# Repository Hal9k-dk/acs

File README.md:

# Hal9k Access Control System

For more information, see https://hal9k.dk/access-control-system/.

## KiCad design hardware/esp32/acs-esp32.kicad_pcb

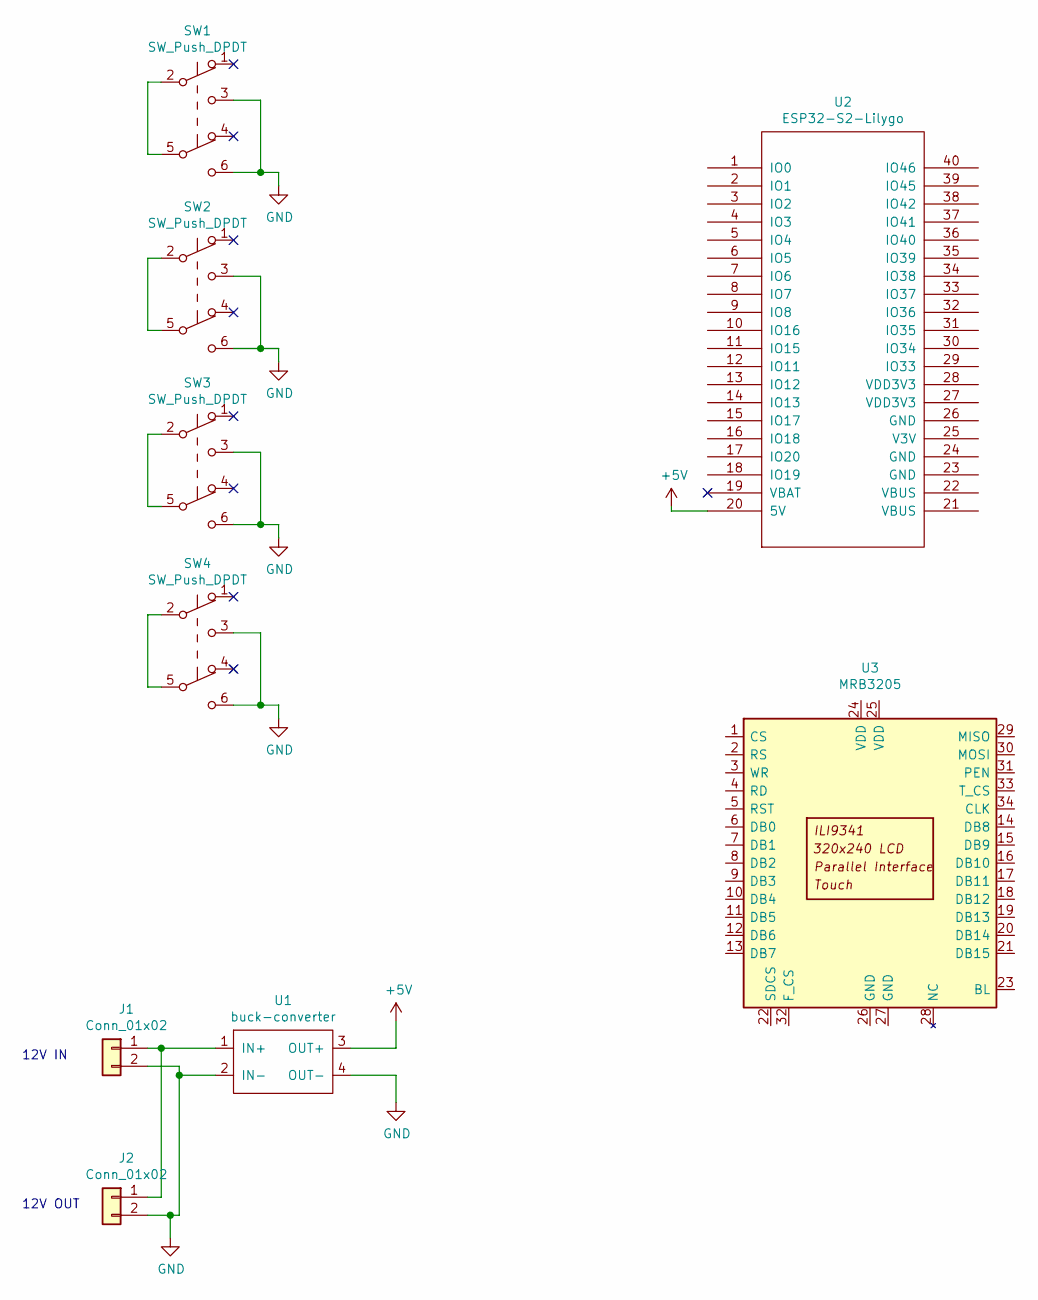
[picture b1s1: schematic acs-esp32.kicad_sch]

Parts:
J1, J2: Conn_01x02; JST_XH_B02B-XH-A_1x02_P2.50mm_Vertical
SW1, SW2, SW3, SW4: SW_Push_DPDT; SW_PUSH_8.5x8.5_DPDT
U1: buck-converter
U2: ESP32-S2-Lilygo; DIP-40_W25.4mm
U3: MRB3205; PinHeader_2x17_P2.54mm_Vertical

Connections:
+5V: U1.3 (OUT+), U2.20 (5V)
GND: J1.2, J2.2, SW1.3 (C), SW1.6 (C), SW2.3 (C), SW2.6 (C), SW3.3 (C), SW3.6 (C), SW4.3 (C), SW4.6 (C), U1.2 (IN-), U1.4 (OUT-)
unnamed: J1.1, J2.1, U1.1 (IN+)
unnamed: SW1.2 (B), SW1.5 (B)
unnamed: SW2.2 (B), SW2.5 (B)
unnamed: SW3.2 (B), SW3.5 (B)
unnamed: SW4.2 (B), SW4.5 (B)

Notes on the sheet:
12V IN
12V OUT

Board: 2 copper layers, 9 parts (0 on the bottom side), 7 nets, no tracks yet.

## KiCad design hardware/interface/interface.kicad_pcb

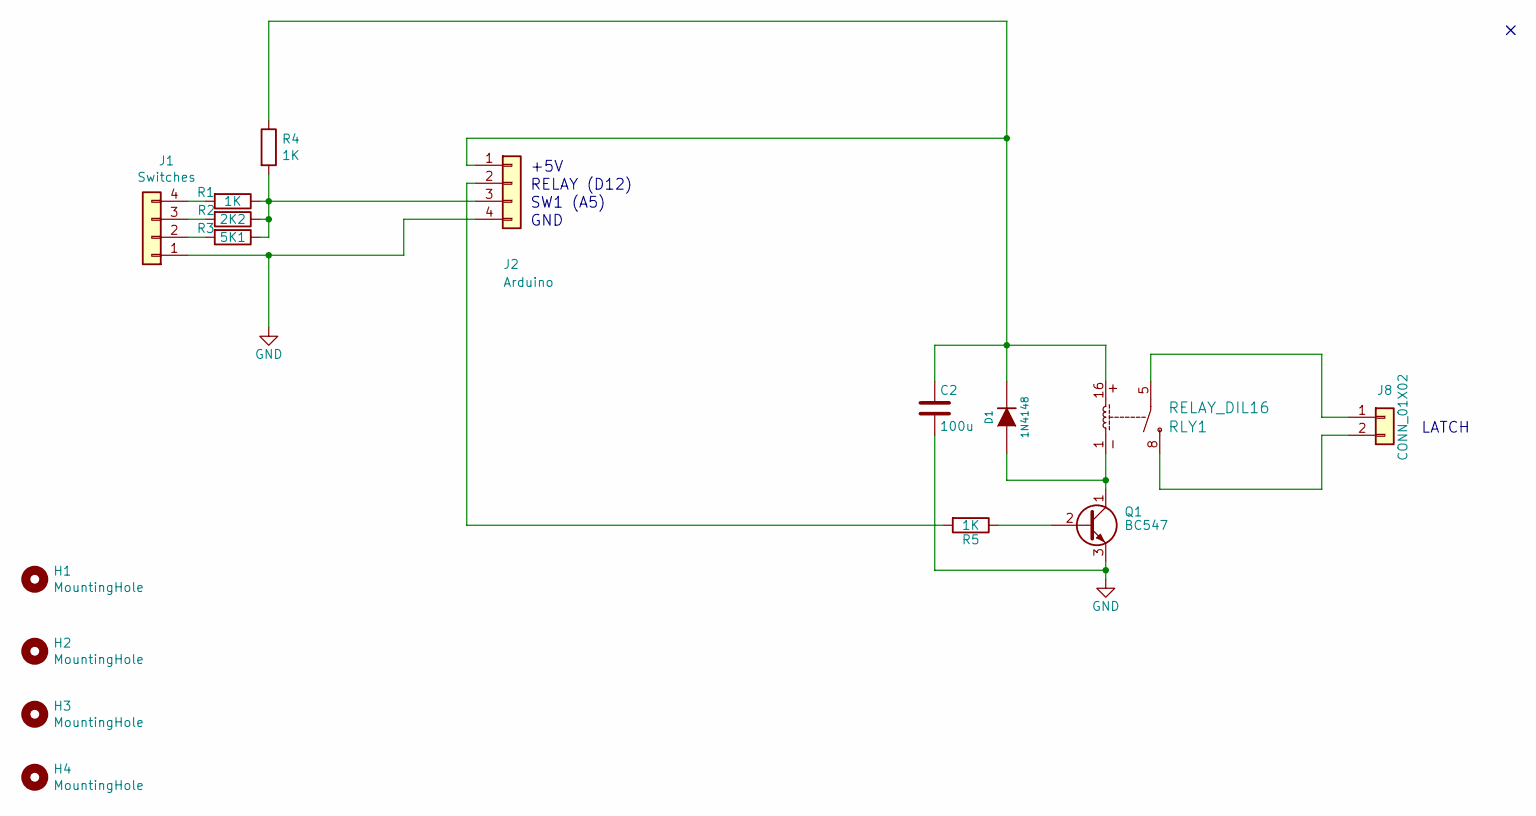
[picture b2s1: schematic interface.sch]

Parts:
C2: 100u; CP_Radial_D10.0mm_P5.00mm
D1: 1N4148; D_DO-35_SOD27_P2.54mm_Vertical_AnodeUp
H1, H2, H3, H4: MountingHole; MountingHole_2.7mm_M2.5
J1: Switches; JST_XH_B04B-XH-A_1x04_P2.50mm_Vertical
J2: Arduino; PinHeader_1x04_P2.54mm_Vertical
J8: CONN_01X02; JST_XH_B02B-XH-A_1x02_P2.50mm_Vertical
Q1: BC547; TO-92_Wide
R1, R4, R5: 1K; R_Axial_DIN0309_L9.0mm_D3.2mm_P5.08mm_Vertical
R2: 2K2; R_Axial_DIN0309_L9.0mm_D3.2mm_P5.08mm_Vertical
R3: 5K1; R_Axial_DIN0309_L9.0mm_D3.2mm_P5.08mm_Vertical
RLY1: RELAY_DIL16; DIP-16_Relay

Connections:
GND: C2.2, J1.1, J2.4, Q1.3 (E)
unnamed: C2.1, D1.2 (K), J2.1, R4.1, RLY1.16
unnamed: D1.1 (A), Q1.1 (C), RLY1.1
unnamed: J1.2, R3.2
unnamed: J1.3, R2.2
unnamed: J1.4, R1.2
unnamed: J2.2, R5.2
unnamed: J2.3, R1.1, R2.1, R3.1, R4.2
unnamed: J8.1, RLY1.5
unnamed: J8.2, RLY1.8
unnamed: Q1.2 (B), R5.1

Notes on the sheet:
LATCH
GND
+5V
RELAY (D12)
SW1 (A5)

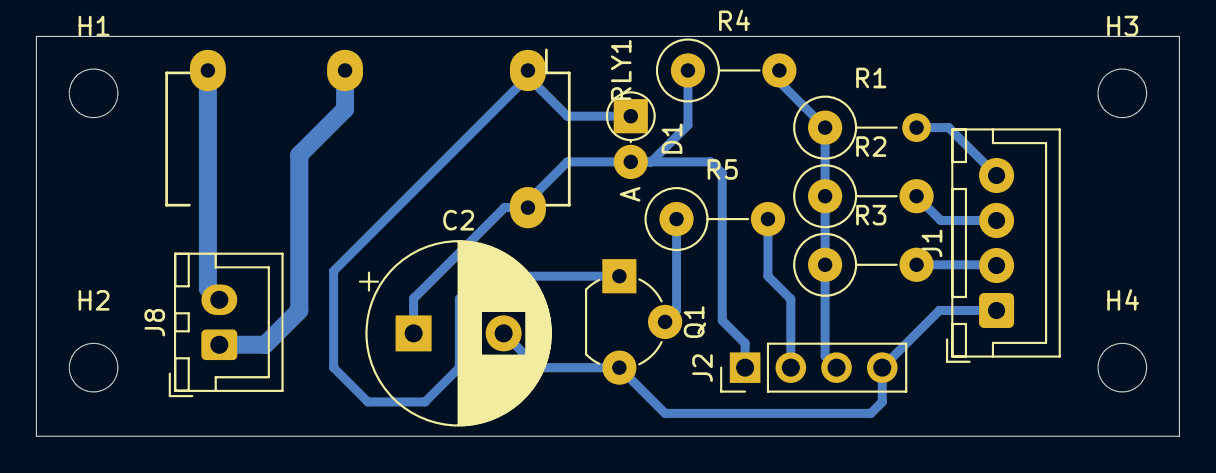
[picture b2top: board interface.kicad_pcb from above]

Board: 2 copper layers, 63.5 x 22.2 mm, 16 parts (0 on the bottom side), 11 nets.

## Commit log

2018-10-27 Add link.
2018-10-27 Include user name.
2018-10-28 Add missing file.
2019-03-14 Check user.active.
2019-03-31 Update.
2019-05-17 Port to OpenSmart HX8352-B display.
2019-05-17 Add test.
2019-05-17 Fix bugs.
2019-05-17 Clear clock.
2019-05-18 Add PCB for switches and relay.
2019-05-18 Enable pullups on switch pins.
2019-05-26 Fix clear for 'c'. Prepare for analog switch input.
2019-05-26 Stuff.
2019-05-26 Read analog switch input.
2019-06-22 Update versions.
2019-06-22 Get rid of warnings.
2019-06-24 Fix size
2019-06-28 Add.
2019-06-28 Work around permission issues.
2019-06-28 Update dependencies.
2019-07-21 Bump version.
2019-07-21 Fix leftover pixels.
2019-07-21 Add OpenSmart compatibility.
2019-07-21 Work around timeout issue.
2019-07-21 Prevent double unlocking.
2019-07-22 Make key press detection more robust.
2019-07-22 Fix serial timeout problem.
2019-08-08 Add automatic exit from Thursday mode.
2019-08-25 Fix stupid bug in LT command.
2020-06-22 Start PCB for reader.
2020-07-17 Adjust for PCB.
2020-07-17 Fix indent.
2020-08-20 Use watchdog.
2020-08-20 Reset timed lock when entering unlocked mode.
2020-08-20 Set stdout to flush immediately.
2020-08-20 Use wrapper script.
2020-08-20 Enlarge LED holes slightly.
2020-08-20 Update for Arch.
2020-08-21 Update buzzer footprint.
2020-08-23 Do not use String.
2020-08-23 Add sound support, fix lots of bugs.
2020-08-23 Add swipe beep.
2020-08-24 First attempt.
2020-08-25 Add hole for connector.
2020-08-26 Do not beep quite so often.
2020-08-26 Use interrupt for beep.
2020-08-28 Rewrite FSA.
2020-08-28 Update LEDs from ISR.
2020-08-28 Optimize setting of idle pattern.
2020-12-18 Adapt for ACS use.
2020-12-18 Add skeleton.
2020-12-19 Read URL/key from settings.yml.
2020-12-21 Implement main loop.
2021-03-05 Detect Danalock port.
2021-03-05 Update gem versions.
2021-03-06 Implement Danalock lock/unlock.
2021-03-06 Implement card unlock for Danalock,
2021-03-11 Run calibration if necessary.
2021-03-12 Add sound when calibrating, and when locking is not possible.
2021-03-16 Add Slack class.
2021-03-17 Handle desired vs actual lock state.
2021-03-17 Show 'Enter' message after swiping card.
2021-03-18 Complain on Slack if lock status is weird, or manual mode has been engaged for too long.
2021-03-18 Handle return to auto mode.
2021-03-20 Add Makefile.
2021-03-20 Update to latest MCUFRIEND version; drop lock support.
2021-03-20 Improve error messages.
2021-03-20 Make large font larger. Reduce program size.
2021-03-20 Make animater use configurable.
2021-03-20 Add filter resistor on supply line.
2021-03-22 Fix various minor issues.
2021-03-23 Fix som cosmetic issues.
2021-03-23 Add erase test.
2021-03-23 Fix bug in E command.
2021-03-26 Fix line spacing.
2021-03-26 Fix small line spacing.
2021-03-26 Rewrite display handling.
2021-03-28 Return to automatic mode when timeout elapses.
2021-03-28 Improve LED handling, make startup faster.
2021-03-28 Add support for button 4.
2021-03-28 Replace relay with button 4.
2021-03-30 Report errors on Slack.
2021-03-30 Add support for Leave button. Fix temp status bug.
2021-03-30 Post to Slack when door is locked again.
2021-03-30 Show manual mode on display.
2021-04-05 Handle echo from Danalock.
2021-04-12 Ensure that after_unlock_fn is cleared.
2021-04-15 Use tee.
2021-04-22 Initialise serial ports first.
2021-04-23 Change user.
2021-05-23 Make it work.
2021-05-23 Inform about closing.
2021-05-28 Tweaks.
2021-05-30 Update for Debian Stretch.
2021-05-30 Update to Rails 5.0.7.2.
2021-05-30 Increase thickness.
2021-05-30 Fix size.
2021-05-30 Add more steps.
2021-06-01 Fix deprecation warning.
2021-06-01 Add OS stuff.
2021-06-01 RST.
2021-06-03 Make BACS work.
2021-06-10 Add Slack output.
2021-06-10 Define last_status.
2021-06-10 Fix logging.
2021-06-20 Add TFT library.
2021-06-21 Add KiCad project.
2021-07-06 Start Dockerification.
2021-07-06 Migrate DB to MariaDB/MySQL.
2021-07-12 Tweak production config for Docker.
2021-07-12 Update for Docker.
2021-07-12 Ignore more.
2021-07-12 Remove migrations.
2021-07-12 Update for MariaDB.
2021-07-14 Use Ruby 3.0.
2021-07-14 Rails 6.
2021-07-17 Remove padding.
2021-07-17 Saving last version for active buzzer.
2021-07-17 Version for passive buzzer.
